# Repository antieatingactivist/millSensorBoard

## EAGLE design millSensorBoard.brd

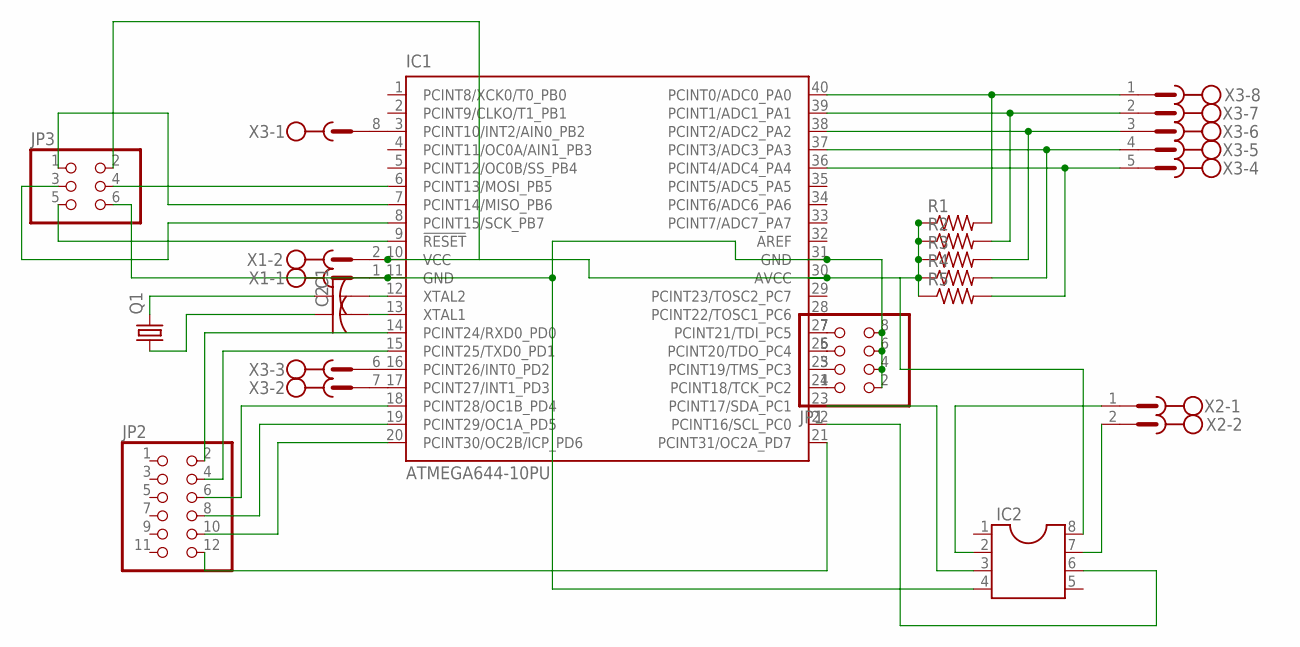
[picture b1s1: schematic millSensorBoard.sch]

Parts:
C1, C2: C-US025-025X050; C025-025X050
IC1: ATMEGA644-10PU; DIL40
IC2: DIL8; DIL08
JP1: PINHD-2X4; 2X04
JP2: PINHD-2X6; 2X06
JP3: PINHD-2X3; 2X03
Q1: CRYSTALHC49S; HC49/S
R1, R2, R3, R4, R5: R-US_0207/10; 0207/10
X1, X2: MSTBV2
X3: MSTBV8

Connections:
unnamed: IC1.23 (PCINT17/SDA_PC1), IC2.3
unnamed: IC1.22 (PCINT16/SCL_PC0), IC2.6
unnamed: IC1.40 (PCINT0/ADC0_PA0), R1.2, X3.1
unnamed: IC1.11 (GND), IC1.31 (GND), IC2.4, JP1.2, JP1.4, JP1.6, JP1.8, JP3.6, X1.1
unnamed: IC1.39 (PCINT1/ADC1_PA1), R2.2, X3.2
unnamed: IC1.38 (PCINT2/ADC2_PA2), R3.2, X3.3
unnamed: IC1.37 (PCINT3/ADC3_PA3), R4.2, X3.4
unnamed: IC1.36 (PCINT4/ADC4_PA4), R5.2, X3.5
unnamed: IC1.17 (PCINT27/INT1_PD3), X3.7
unnamed: IC1.16 (PCINT26/INT0_PD2), X3.6
unnamed: IC1.3 (PCINT10/INT2/AIN0_PB2), X3.8
unnamed: IC1.14 (PCINT24/RXD0_PD0), JP2.2
unnamed: IC1.15 (PCINT25/TXD0_PD1), JP2.4
unnamed: IC1.18 (PCINT28/OC1B_PD4), JP2.6
unnamed: IC1.24 (PCINT18/TCK_PC2), JP1.1
unnamed: IC1.25 (PCINT19/TMS_PC3), JP1.3
unnamed: IC1.26 (PCINT20/TDO_PC4), JP1.5
unnamed: IC1.27 (PCINT21/TDI_PC5), JP1.7
unnamed: IC1.7 (PCINT14/MISO_PB6), JP3.1
unnamed: IC1.8 (PCINT15/SCK_PB7), JP3.3
unnamed: IC1.9 (!RESET), JP3.5
unnamed: IC1.6 (PCINT13/MOSI_PB5), JP3.4
unnamed: C1.2, IC1.12 (XTAL2)
unnamed: C2.2, IC1.13 (XTAL1)
unnamed: C1.1, Q1.2
unnamed: C2.1, Q1.1
unnamed: IC1.19 (PCINT29/OC1A_PD5), JP2.8
unnamed: IC2.2, X2.1
unnamed: IC2.7, X2.2
unnamed: IC1.20 (PCINT30/OC2B/ICP_PD6), JP2.10
unnamed: IC1.21 (PCINT31/OC2A_PD7), JP2.12
unnamed: IC1.10 (VCC), IC1.30 (AVCC), IC2.8, JP3.2, R1.1, R2.1, R3.1, R4.1, R5.1, X1.2

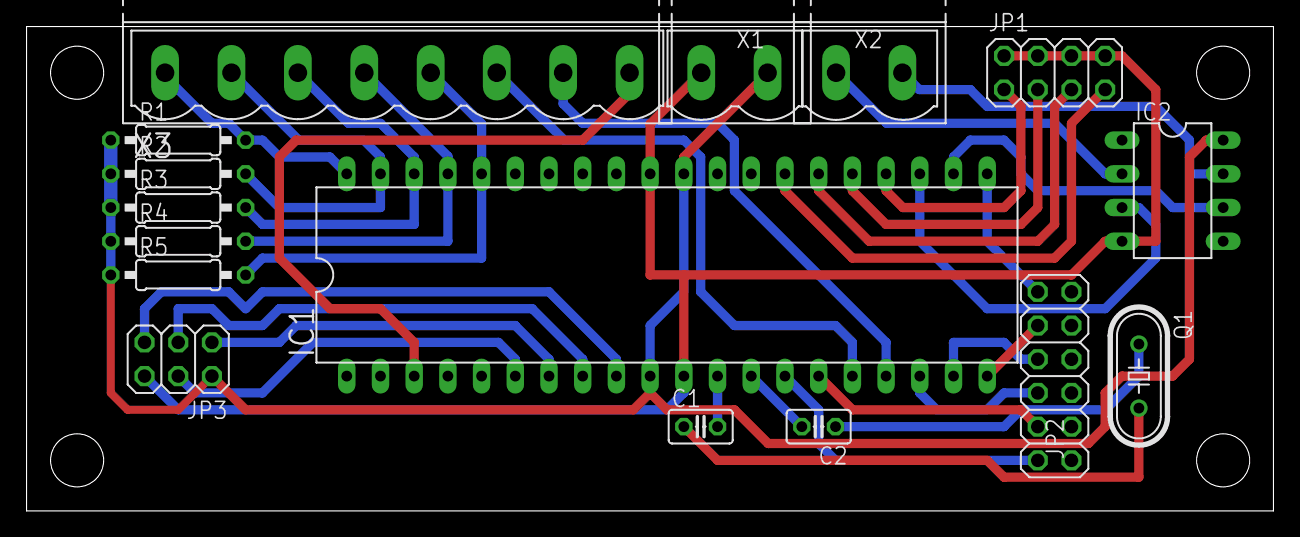
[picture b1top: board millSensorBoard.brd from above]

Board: 2 copper layers, 94.0 x 36.5 mm, 16 parts (0 on the bottom side), 32 nets.

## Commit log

2021-03-11 initial upload
2021-03-12 added image
2021-03-12 organized
2021-03-12 remove DS store
